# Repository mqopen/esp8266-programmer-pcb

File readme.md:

# ESP8266 programmer

This is part of [mqopen](http://mqopen.org) project.

## Features

 - Board dimensions: 1800 x 1000 mils (45.72 x 25.4 mm).
 - FT232RL chip.
 - Connected using mini USB socket (4 legs SMD).
 - PWR, RX and TX LEDs.
 - 10 pin AVR like header for programming ribbon cable.

## Get board

You can order PCB on this [link](http://dirtypcbs.com/view.php?share=20024&accesskey=b40cd2f50915caacdd38e3f2a6016732).

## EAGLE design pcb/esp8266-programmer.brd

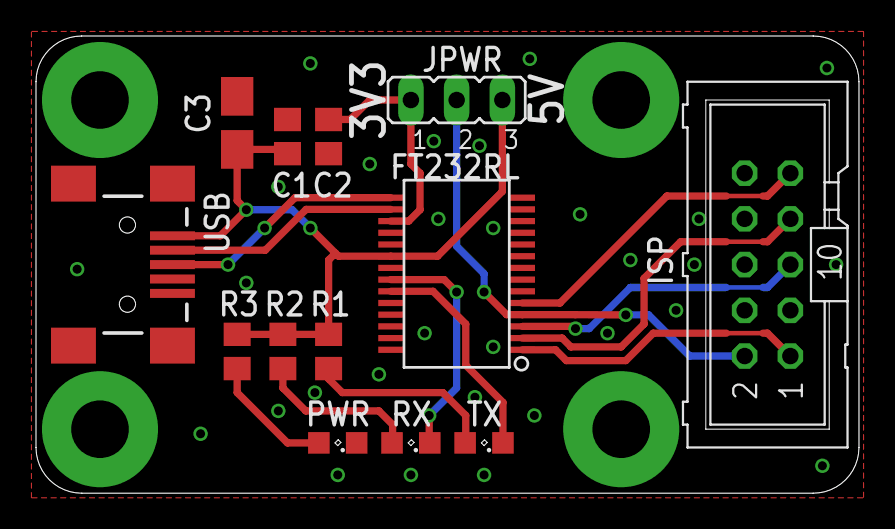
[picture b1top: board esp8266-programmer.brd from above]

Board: 2 copper layers, 45.7 x 25.4 mm, 14 parts (1 on the bottom side), 15 nets.

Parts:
C1, C2: 100nF; C0805
C3: 10uF; A/3216-18W
FT232RL: FT232RLSSOP; SSOP28DB
ISP: AVR-ISP-10ML; ML10
JPWR: JP2
LOGO1: OSHW-LOGOL; OSHW-LOGO-L
PWR: SML0805
R1, R2: 1K; R0805
R3: 330; R0805
RX: SML0805
TX: SML0805
USB: USBSMD; USB-MINIB

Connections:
+3V3: C2.1, FT232RL.17, JPWR.1
+5V: C1.1, C3.+, FT232RL.20, JPWR.3, R1.2, R2.2, R3.1, USB.VBUS
DTR: FT232RL.2, ISP.7
GND: C1.2, C2.2, C3.-, FT232RL.7, FT232RL.18, FT232RL.21, FT232RL.25, FT232RL.26, ISP.3, ISP.4, ISP.6, ISP.8, ISP.10, PWR.C, USB.GND
unnamed: PWR.A, R3.2
unnamed: R1.1, TX.A
unnamed: R2.1, RX.A
PWROUT: FT232RL.4, ISP.2, JPWR.2
RST: FT232RL.3, ISP.5
RX: FT232RL.22, RX.C
RXD: FT232RL.5, ISP.9
TX: FT232RL.23, TX.C
TXD: FT232RL.1, ISP.1
USBDM: FT232RL.16, USB.D-
USBDP: FT232RL.15, USB.D+

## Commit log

2016-04-21 Initial commit.
2016-04-22 Initial board design.
2016-05-27 Final board design.
2016-05-27 Added changelog.
2016-05-27 Added readme file.
2016-05-27 Added schematics file.

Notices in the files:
parts and their libraries:
SparkFun-Connectors: Licensing: Creative Commons ShareAlike 4.0 International - https://creativecommons.org/licenses/by-sa/4.0
